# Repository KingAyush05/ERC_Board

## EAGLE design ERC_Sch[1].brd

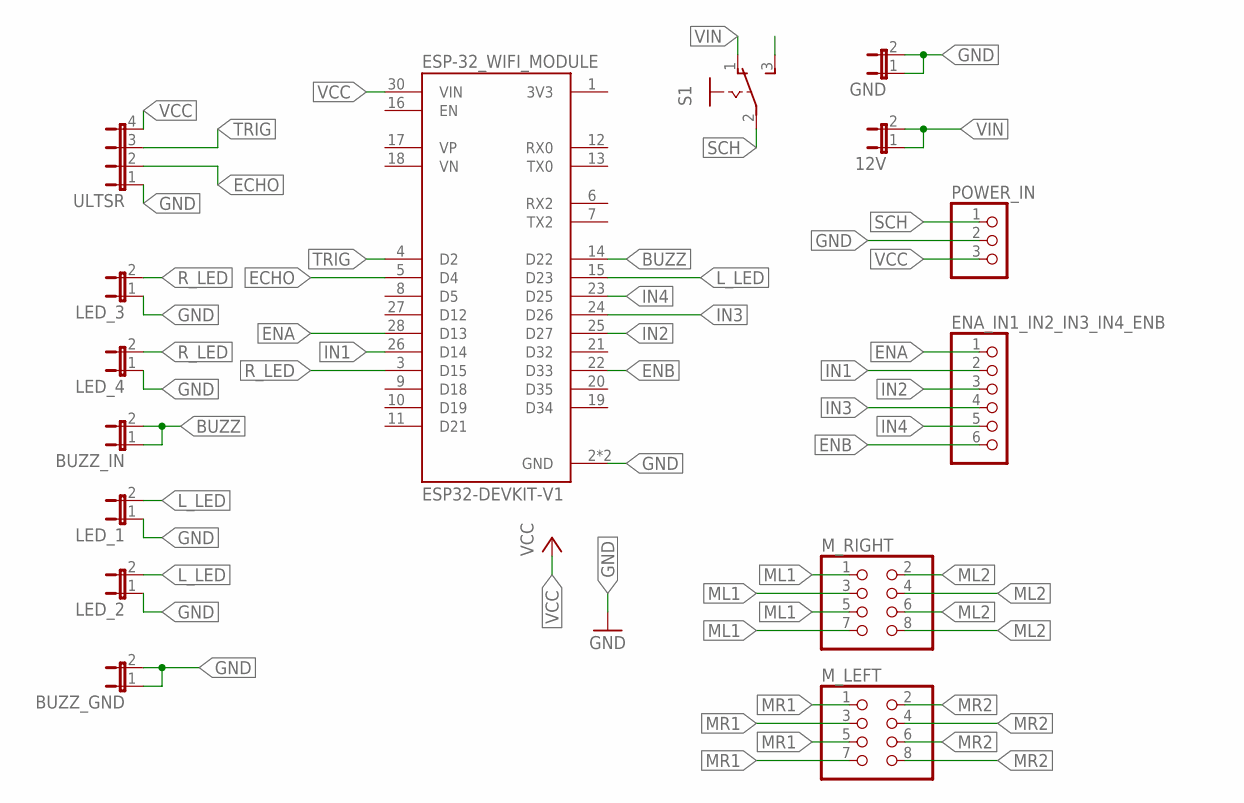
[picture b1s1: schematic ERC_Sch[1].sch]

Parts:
12V: JP1E; JP1
BUZZ_GND: JP1E; JP1
BUZZ_IN: JP1E; JP1
ENA_IN1_IN2_IN3_IN4_ENB: PINHD-1X6; 1X06
ESP-32_WIFI_MODULE: ESP32-DEVKIT-V1; MODULE_ESP32_DEVKIT_V1
GND: JP1E; JP1
LED_1, LED_2, LED_3, LED_4: JP1E; JP1
M_LEFT: PINHD-2X4; 2X04
M_RIGHT: PINHD-2X4; 2X04
POWER_IN: PINHD-1X3; 1X03
S1: 255SB
ULTSR: JP4E; JP4

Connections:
BUZZ: BUZZ_IN.1, BUZZ_IN.2, ESP-32_WIFI_MODULE.14 (D22)
ECHO: ESP-32_WIFI_MODULE.5 (D4), ULTSR.2
ENA: ENA_IN1_IN2_IN3_IN4_ENB.1, ESP-32_WIFI_MODULE.28 (D13)
ENB: ENA_IN1_IN2_IN3_IN4_ENB.6, ESP-32_WIFI_MODULE.22 (D33)
GND: BUZZ_GND.1, BUZZ_GND.2, ESP-32_WIFI_MODULE.2 (GND), ESP-32_WIFI_MODULE.29 (GND), GND.1, GND.2, LED_1.1, LED_2.1, LED_3.1, LED_4.1, POWER_IN.2, ULTSR.1
IN1: ENA_IN1_IN2_IN3_IN4_ENB.2, ESP-32_WIFI_MODULE.26 (D14)
IN2: ENA_IN1_IN2_IN3_IN4_ENB.3, ESP-32_WIFI_MODULE.25 (D27)
IN3: ENA_IN1_IN2_IN3_IN4_ENB.4, ESP-32_WIFI_MODULE.24 (D26)
IN4: ENA_IN1_IN2_IN3_IN4_ENB.5, ESP-32_WIFI_MODULE.23 (D25)
L_LED: ESP-32_WIFI_MODULE.15 (D23), LED_1.2, LED_2.2
ML1: M_RIGHT.1, M_RIGHT.3, M_RIGHT.5, M_RIGHT.7
ML2: M_RIGHT.2, M_RIGHT.4, M_RIGHT.6, M_RIGHT.8
MR1: M_LEFT.1, M_LEFT.3, M_LEFT.5, M_LEFT.7
MR2: M_LEFT.2, M_LEFT.4, M_LEFT.6, M_LEFT.8
R_LED: ESP-32_WIFI_MODULE.3 (D15), LED_3.2, LED_4.2
SCH: POWER_IN.1, S1.2
TRIG: ESP-32_WIFI_MODULE.4 (D2), ULTSR.3
VCC: ESP-32_WIFI_MODULE.30 (VIN), POWER_IN.3, ULTSR.4
VIN: 12V.1, 12V.2, S1.1 (O)

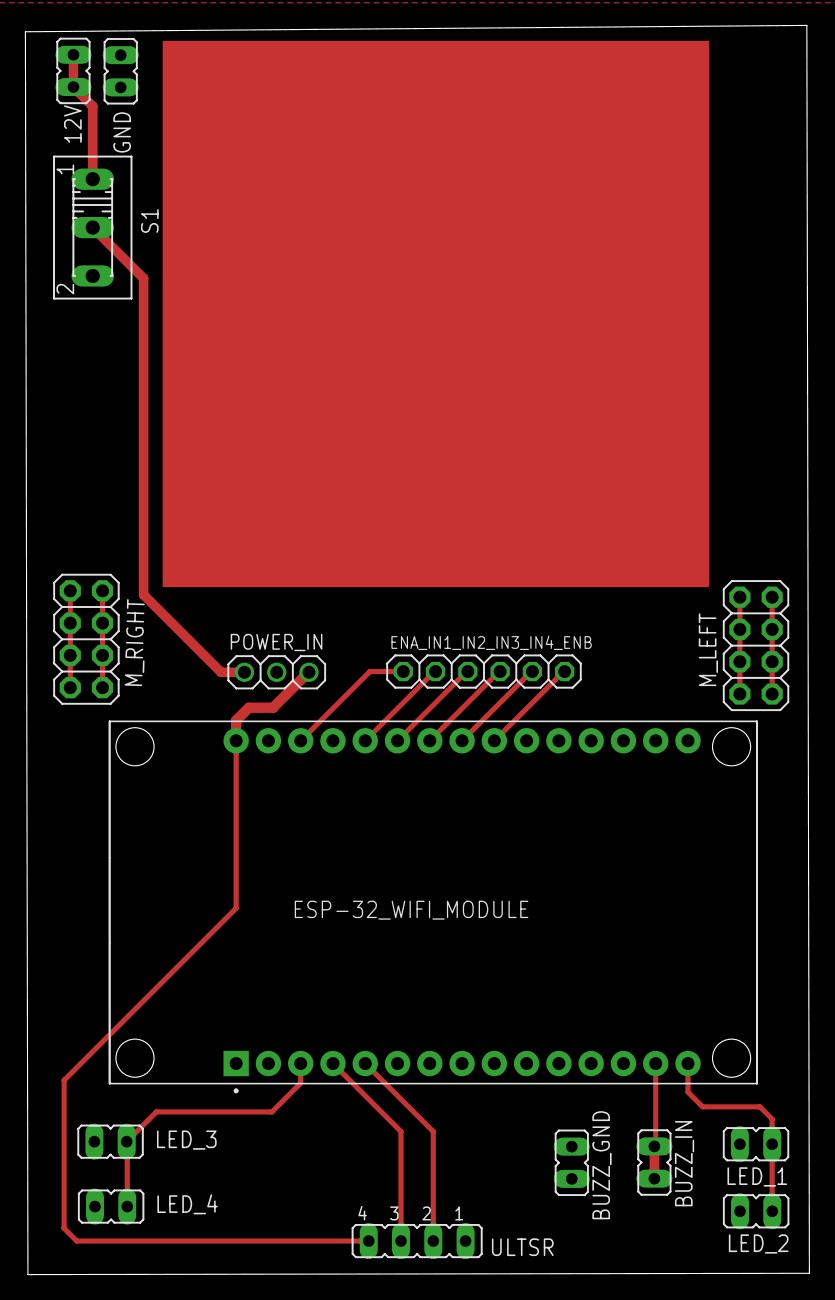
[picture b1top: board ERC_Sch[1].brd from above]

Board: 2 copper layers, 61.7 x 98.3 mm, 15 parts (0 on the bottom side), 19 nets.

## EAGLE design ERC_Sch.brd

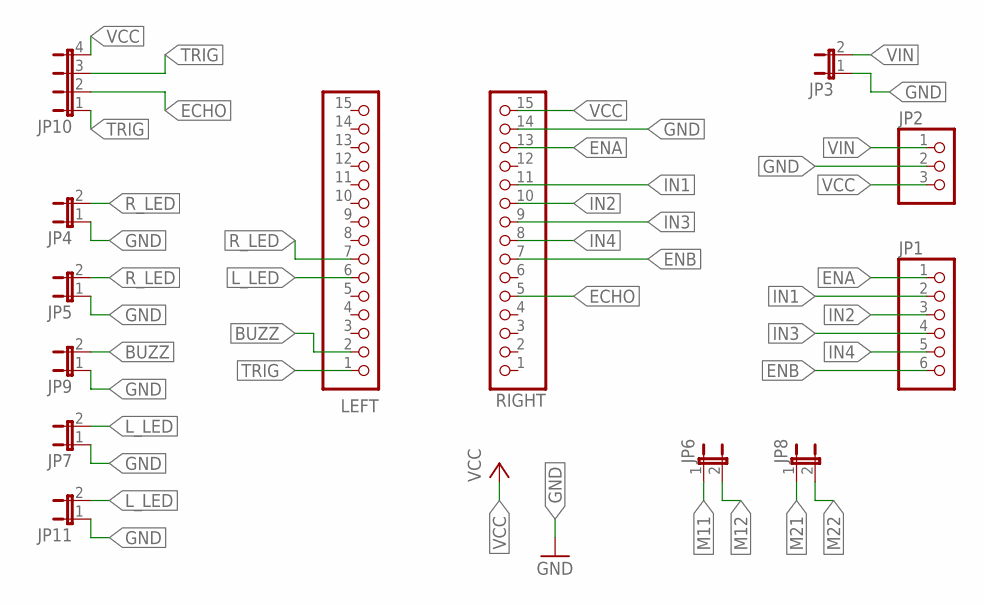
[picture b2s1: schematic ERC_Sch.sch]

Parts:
JP1: PINHD-1X6; 1X06
JP2: PINHD-1X3; 1X03
JP3, JP4, JP5, JP6, JP7, JP8, JP9, JP11: JP1E; JP1
JP10: JP4E; JP4
LEFT: PINHD-1X15; 1X15
RIGHT: PINHD-1X15; 1X15

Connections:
BUZZ: JP9.2, LEFT.2
ECHO: JP10.2, RIGHT.5
ENA: JP1.1, RIGHT.13
ENB: JP1.6, RIGHT.7
GND: JP2.2, JP3.1, JP4.1, JP5.1, JP7.1, JP9.1, JP11.1, RIGHT.14
IN1: JP1.2, RIGHT.11
IN2: JP1.3, RIGHT.10
IN3: JP1.4, RIGHT.9
IN4: JP1.5, RIGHT.8
L_LED: JP7.2, JP11.2, LEFT.6
M11: JP6.1
M12: JP6.2
M21: JP8.1
M22: JP8.2
R_LED: JP4.2, JP5.2, LEFT.7
TRIG: JP10.1, JP10.3, LEFT.1
VCC: JP2.3, JP10.4, RIGHT.15
VIN: JP2.1, JP3.2

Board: 2 copper layers, 13 parts (0 on the bottom side), 14 nets, no tracks yet.
